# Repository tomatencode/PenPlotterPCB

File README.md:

# Pen Plotter Controller Board

Eine selbst entworfene PCB-Steuerplatine für einen DIY Pen Plotter, entwickelt in KiCad. Die Platine steuert zwei Schrittmotoren für die XY-Bewegung, einen Servo für den Stifthub und übernimmt Benutzerführung sowie Energiemanagement vollständig auf einer einzigen Platine.

## Funktionen

- **ESP32** – Haupt-Mikrocontroller (Breakout aufgelötet) für Bewegungssteuerung und Logik
- **2× TMC2209** – Schrittmotortreiber (Breakouts aufgelötet) mit UART-Konfiguration, stealthChop und stallGuard
- **SG90 Servo** – Stift-Auf/Ab-Mechanismus
- **I2C LCD-Display** – Angeschlossen über Steckverbinder
- **Drehgeber** – Manuelle Steuerung und Menünavigation über Steckverbinder
- **Buzzer** – Akustisches Feedback
- **Lüfter** – Transistorgesteuerter Lüfter zur Kühlung der Motortreiber
- **5V Buck Converter** – (Breakout aufgelötet) Erzeugt die interne 5V-Versorgungsschiene aus 24V
- **24V DC-Eingang** – Versorgung über externen Transformator (DC-Hohlbuchse)

## Stromversorgungsarchitektur

| Schiene | Quelle                          | Verbraucher                            |
|---------|---------------------------------|----------------------------------------|
| 24 V    | Externer Transformator (DC-Buchse) | TMC2209 Motorspannung, Lüfter       |
| 5 V     | Buck Converter Breakout         | ESP32, Servo, Buzzer, LCD              |
| 3,3 V   | Interner LDO des ESP32          | TMC2209 Logikspannung, Drehgeber       |

## Platinenübersicht

### Schaltplan

### PCB-Layout

### 3D-Ansicht

## Entwickelt mit

- [KiCad](https://www.kicad.org/) – Schaltplan und PCB-Layout

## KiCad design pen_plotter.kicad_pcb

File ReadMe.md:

# Pen Plotter Controller Board

A custom PCB controller for a DIY pen plotter, designed in KiCad. The board drives two stepper motors for XY movement, a servo for pen lift, and handles all user interface and power management on a single board.

## Features

- **ESP32** microcontroller (breakout soldered onto PCB) for motion control and logic
- **2× TMC2209** stepper motor drivers (breakouts soldered onto PCB) with UART configuration support
- **SG90 servo** for pen up/down control
- **Buzzer** for audio feedback
- **Fan** driven via transistor for driver cooling
- **I2C LCD display** via connector
- **Rotary encoder** via connector for manual control
- **5V buck converter** (breakout soldered onto PCB) for onboard 5V power rail
- **24V DC input** from external transformer

## Board Overview

### Schematic

### PCB Layout

### 3D View

## Power Architecture

| Rail | Source | Consumers |
|------|--------|-----------|
| 24V | External transformer (DC jack) | TMC2209 motor voltage, fan |
| 5V | Buck converter breakout | ESP32, servo, buzzer, LCD |
| 3.3V | LDO of ESP32 | TMC2209 logic voltage, Rortary encoder|

## Hardware

| Component | Description |
|-----------|-------------|
| ESP32 | Main microcontroller, Wi-Fi/BT capable |
| TMC2209 (×2) | Stepper drivers with UART, stealthChop, stallGuard |
| SG90 | Servo for pen lift mechanism |
| Buck converter | 24V → 5V step-down |
| LCD | I2C character or graphic display |
| Rotary encoder | For manual jog / menu navigation |

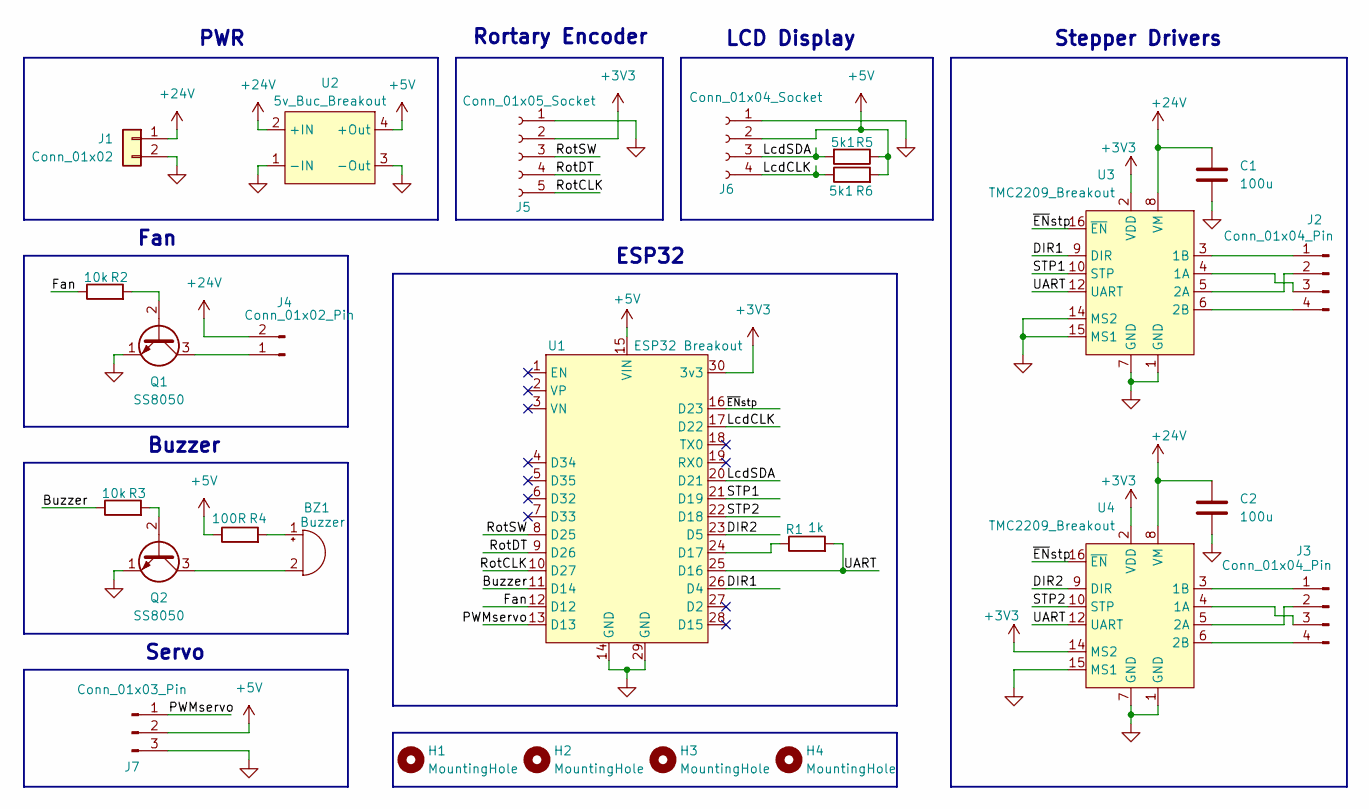
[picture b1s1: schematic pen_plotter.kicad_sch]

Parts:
BZ1: Buzzer; Buzzer_12x9.5RM7.6
C1, C2: 100u; C_Radial_D5.0mm_H7.0mm_P2.00mm
H1, H2, H3, H4: MountingHole; MountingHole_3.2mm_M3
J1: Conn_01x02; TerminalBlock_MaiXu_MX126-5.0-02P_1x02_P5.00mm
J2, J3: Conn_01x04_Pin; PinHeader_1x04_P2.54mm_Vertical
J4: Conn_01x02_Pin; PinHeader_1x02_P2.54mm_Vertical
J5: Conn_01x05_Socket; PinSocket_1x05_P2.54mm_Vertical
J6: Conn_01x04_Socket; PinSocket_1x04_P2.54mm_Vertical
J7: Conn_01x03_Pin; PinHeader_1x03_P2.54mm_Vertical
Q1, Q2: SS8050; TO-92
R1: 1k; R_Axial_DIN0207_L6.3mm_D2.5mm_P10.16mm_Horizontal
R2, R3: 10k; R_Axial_DIN0207_L6.3mm_D2.5mm_P10.16mm_Horizontal
R4: 100R; R_Axial_DIN0207_L6.3mm_D2.5mm_P10.16mm_Horizontal
R5, R6: 5k1; R_Axial_DIN0207_L6.3mm_D2.5mm_P10.16mm_Horizontal
U1: ESP32 Breakout; ESP32_Breakout
U2: 5v_Buc_Breakout; 5V_Buc_Breakout
U3, U4: TMC2209_Breakout

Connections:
+3V3: J5.2, U1.30 (3v3), U3.2 (VDD), U4.2 (VDD), U4.14 (MS2)
+5V: J6.2, J7.2, R4.1, R5.1, R6.2, U1.15 (VIN), U2.4 (+Out)
+24V: C1.1, C2.1, J1.1, J4.2, U2.2 (+IN), U3.8 (VM), U4.8 (VM)
/Buzzer: R3.1, U1.11 (D14)
/DIR1: U1.26 (D4), U3.9 (DIR)
/DIR2: U1.23 (D5), U4.9 (DIR)
/Fan: R2.1, U1.12 (D12)
/LcdCLK: J6.4, R6.1, U1.17 (D22)
/LcdSDA: J6.3, R5.2, U1.20 (D21)
/PWMservo: J7.1, U1.13 (D13)
/RotCLK: J5.5, U1.10 (D27)
/RotDT: J5.4, U1.9 (D26)
/RotSW: J5.3, U1.8 (D25)
/STP1: U1.21 (D19), U3.10 (STP)
/STP2: U1.22 (D18), U4.10 (STP)
/UART: R1.2, U1.25 (D16), U3.12 (UART), U4.12 (UART)
/~ENstp: U1.16 (D23), U3.16 (~EN), U4.16 (~EN)
GND: C1.2, C2.2, J1.2, J5.1, J6.1, J7.3, Q1.1 (E), Q2.1 (E), U1.14 (GND), U1.29 (GND), U2.1 (-IN), U2.3 (-Out), U3.1 (GND), U3.7 (GND), U3.14 (MS2), U3.15 (MS1), U4.1 (GND), U4.7 (GND), U4.15 (MS1)
unnamed: BZ1.1 (+), R4.2
unnamed: BZ1.2 (-), Q2.3 (C)
unnamed: J2.1, U3.3 (1B)
unnamed: J2.2, U3.5 (2A)
unnamed: J2.3, U3.4 (1A)
unnamed: J2.4, U3.6 (2B)
unnamed: J3.1, U4.3 (1B)
unnamed: J3.2, U4.5 (2A)
unnamed: J3.3, U4.4 (1A)
unnamed: J3.4, U4.6 (2B)
unnamed: J4.1, Q1.3 (C)
unnamed: Q1.2 (B), R2.2
unnamed: Q2.2 (B), R3.2
unnamed: R1.1, U1.24 (D17)

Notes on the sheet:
Stepper Drivers
Rortary Encoder
LCD Display
Buzzer
PWR
Servo
Fan
ESP32

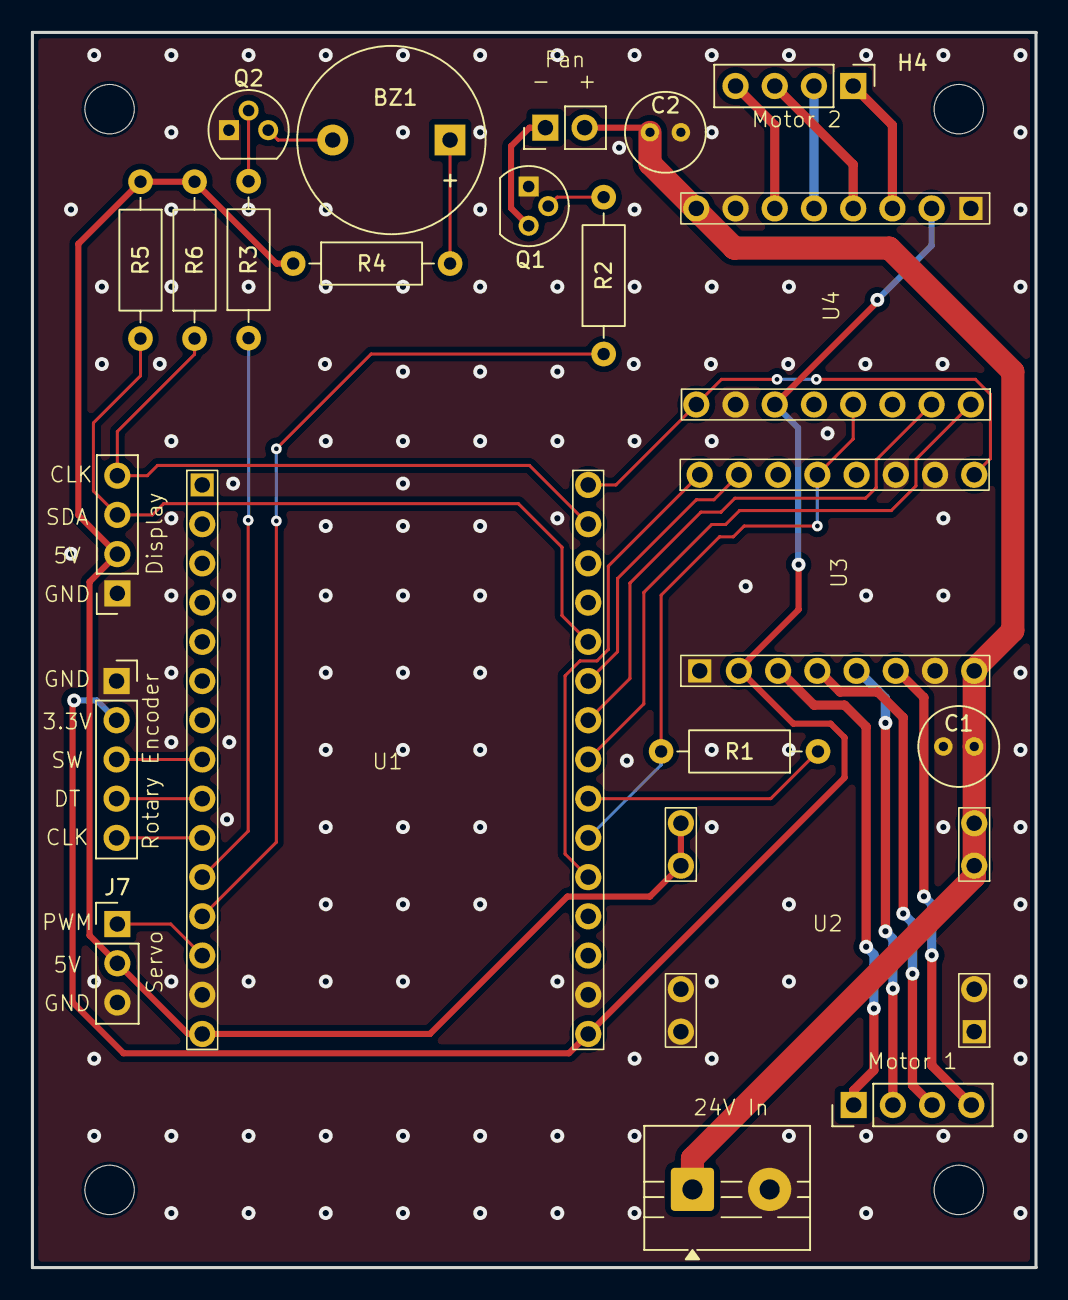
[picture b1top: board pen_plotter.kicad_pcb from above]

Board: 2 copper layers, 65.0 x 80.0 mm, 26 parts (0 on the bottom side), 32 nets.

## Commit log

2026-05-22 readme
2026-05-22 better readme
2026-05-22 corrected mistakes in readme
2026-05-22 readme in german
